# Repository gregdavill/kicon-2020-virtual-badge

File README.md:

# KiCon 2020 Virtual Badge by Greg Davill

Based off the design+template by [Thomas Flummer](https://gitlab.com/flummer/kicon-2020-virtual-badge)

I was inspired by the design Thomas made, and wanted to try and extend the badge with more LEDs. I'm using a similar architecture to the LED panels on the d20 and small LED cube I built, except this only has 1 colour of LED in the Matrix.

## Firmware

I've not coded up firmware for a display like this with a microcontroller before, and I've had trouble with the SAMD21's DMA controller and cyclic descriptors in the past. The display will require constant attention from the SAMD as it is a multiplexed display, I'm hoping that implementing a framebuffer + Binary Coded Modulation will be possible.

## Assembly

The LED matrix is 32x16. Or 512 individual LEDs, these are all 0402 in size, so manual assembly may not be for the casual electronics enthusiast.
At any rate I'd recommend using a solderpaste stencil and reflow oven.

## Making your own

If you want to make your own, I have included the gerbers, in case you don't want to install the nightly version.
The board is 4 layers mostly to assist in routing of the matrix. The cost difference between 2L and 4L at JLC is only $5 on their barebones service.

## Please share

If you decide to make this badge or a variant of it, please share images so we can all see it and get inspired. If sharing on social media, please use the #badgelife tag and please let [me](https://twitter.com/gregdavill) and [thomas](https://thomasflummer.com/) know, I would love to see what you have made!

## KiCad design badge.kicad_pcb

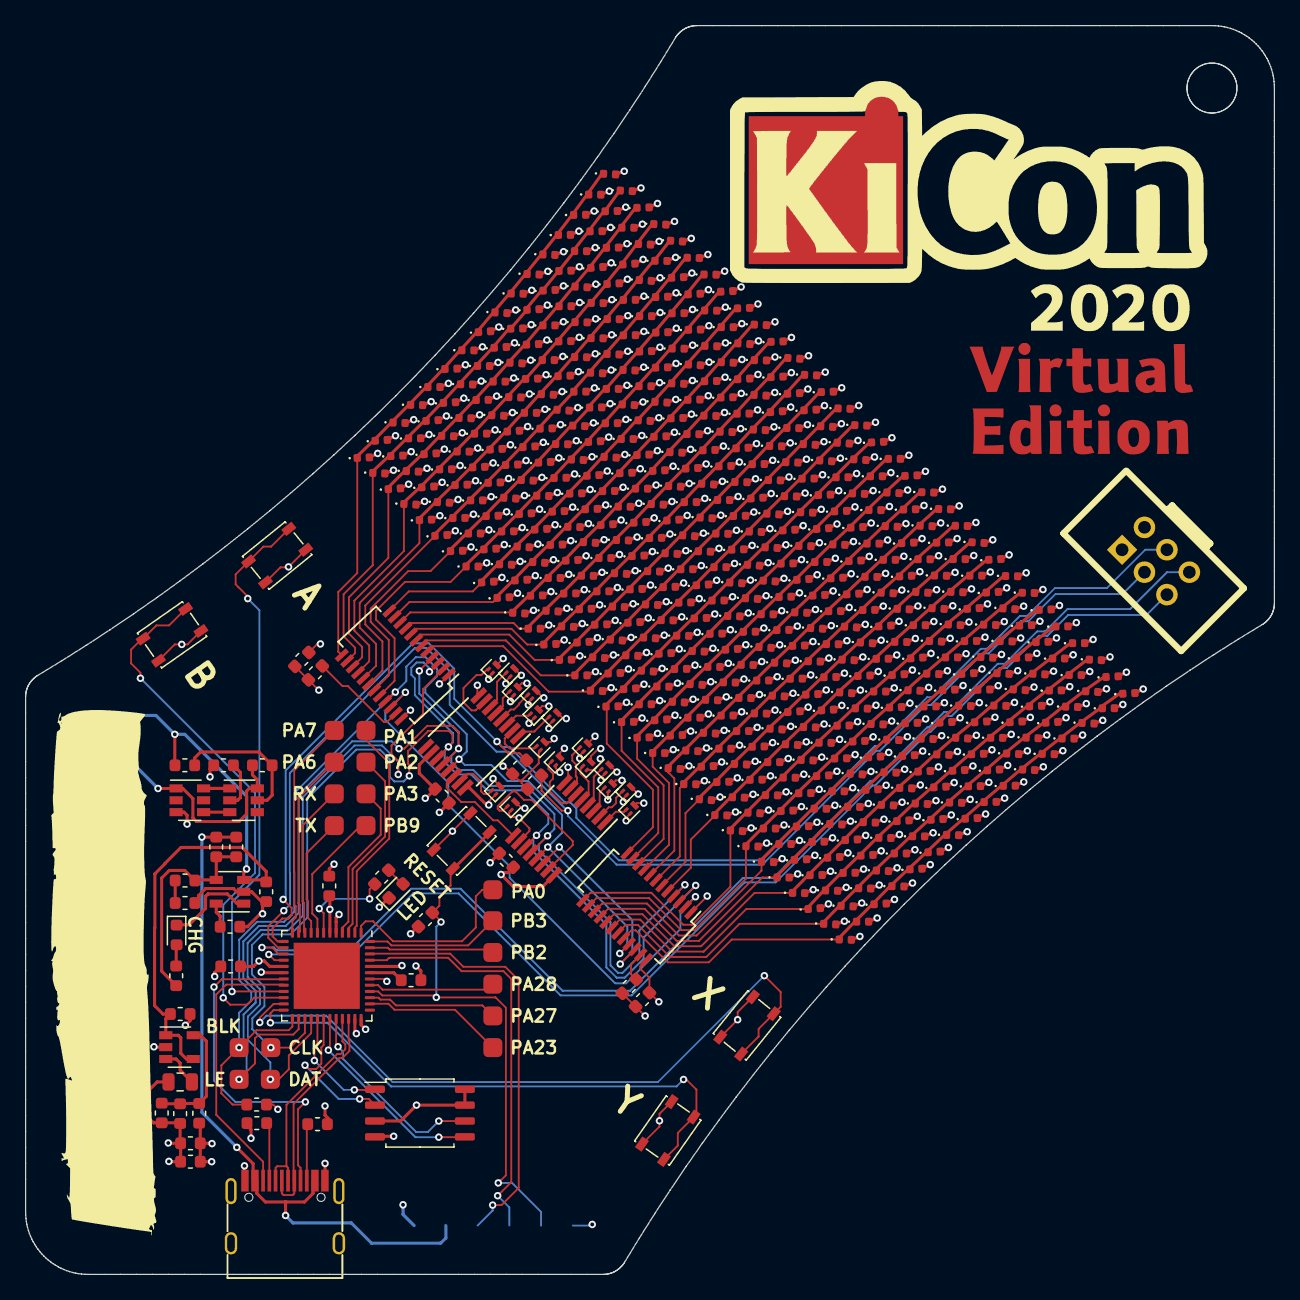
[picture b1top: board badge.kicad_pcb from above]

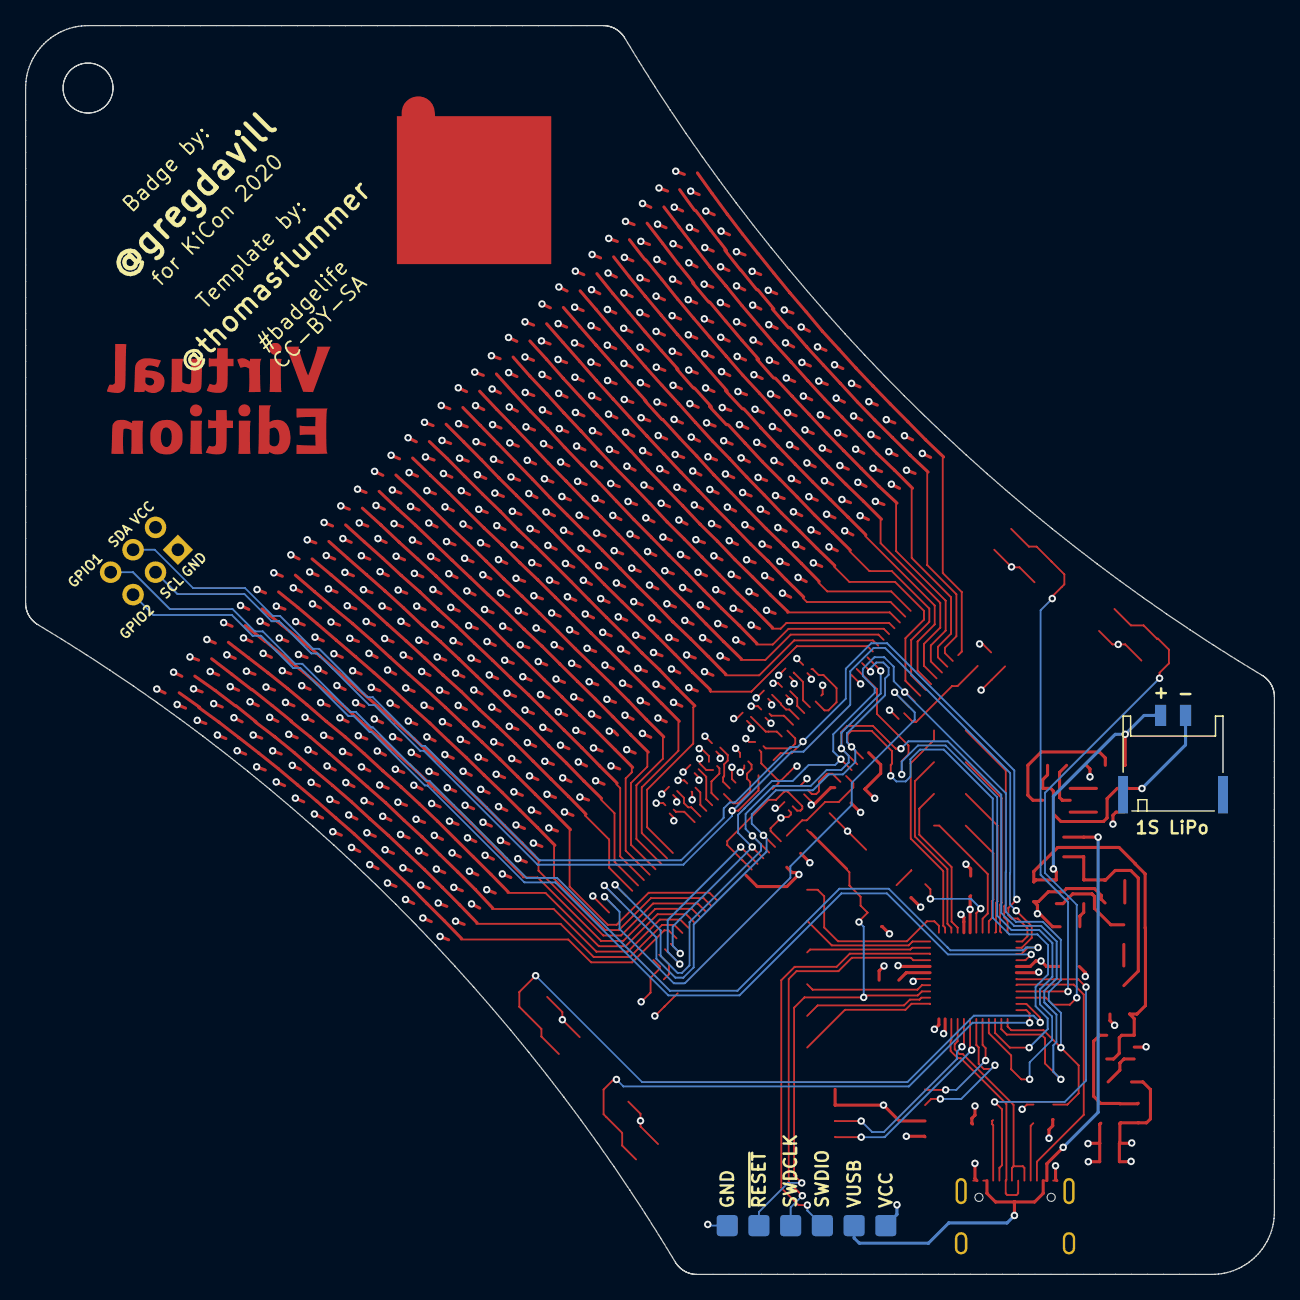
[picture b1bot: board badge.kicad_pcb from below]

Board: 4 copper layers, 100.0 x 100.0 mm, 600 parts (2 on the bottom side), 127 nets.

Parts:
C1, C2, C3, C4, C6, C8, C11: 100nF; C_0603_1608Metric
C5: 1uF; C_0603_1608Metric
C7, C9, C13, C14: 10uF; C_0603_1608Metric
C10: 10pF; C_0603_1608Metric
C12: 4.7uF; C_0603_1608Metric
D1, D2, D3, D4, D5, D6, D7, D8, D9, D10, D11, D12, D13, D14, D15, D16, D17, D18, D19, D20, D21, D22, D23, D24, D25, D26, D27, D28, D29, D30, D31, D32, D33, D34, D35, D36, D37, D38, D39, D40, D41, D42, D43, D44, D45, D46, D47, D48, D49, D50, D51, D52, D53, D54, D55, D56, D57, D58, D59, D60, D61, D62, D63, D64, D65, D66, D67, D68, D69, D70, D71, D72, D73, D74, D75, D76, D77, D78, D79, D80, D81, D82, D83, D84, D85, D86, D87, D88, D89, D90, D91, D92, D93, D94, D95, D96, D97, D98, D99, D100, D101, D102, D103, D104, D105, D106, D107, D108, D109, D110, D111, D112, D113, D114, D115, D116, D117, D118, D119, D120, D121, D122, D123, D124, D125, D126, D127, D128, D129, D130, D131, D132, D133, D134, D135, D136, D137, D138, D139, D140, D141, D142, D143, D144, D145, D146, D147, D148, D149, D150, D151, D152, D153, D154, D155, D156, D157, D158, D159, D160, D161, D162, D163, D164, D165, D166, D167, D168, D169, D170, D171, D172, D173, D174, D175, D176, D177, D178, D179, D180, D181, D182, D183, D184, D185, D186, D187, D188, D189, D190, D191, D192, D193, D194, D195, D196, D197, D198, D199, D200, D201, D202, D203, D204, D205, D206, D207, D208, D209, D210, D211, D212, D213, D214, D215, D216, D217, D218, D219, D220, D221, D222, D223, D224, D225, D226, D227, D228, D229, D230, D231, D232, D233, D234, D235, D236, D237, D238, D239, D240, D241, D242, D243, D244, D245, D246, D247, D248, D249, D250, D251, D252, D253, D254, D255, D256, D257, D258, D259, D260, D261, D262, D263, D264, D265, D266, D267, D268, D269, D270, D271, D272, D273, D274, D275, D276, D277, D278, D279, D280, D281, D282, D283, D284, D285, D286, D287, D288, D289, D290, D291, D292, D293, D294, D295, D296, D297, D298, D299, D300, D301, D302, D303, D304, D305, D306, D307, D308, D309, D310, D311, D312, D313, D314, D315, D316, D317, D318, D319, D320, D321, D322, D323, D324, D325, D326, D327, D328, D329, D330, D331, D332, D333, D334, D335, D336, D337, D338, D339, D340, D341, D342, D343, D344, D345, D346, D347, D348, D349, D350, D351, D352, D353, D354, D355, D356, D357, D358, D359, D360, D361, D362, D363, D364, D365, D366, D367, D368, D369, D370, D371, D372, D373, D374, D375, D376, D377, D378, D379, D380, D381, D382, D383, D384, D385, D386, D387, D388, D389, D390, D391, D392, D393, D394, D395, D396, D397, D398, D399, D400, D401, D402, D403, D404, D405, D406, D407, D408, D409, D410, D411, D412, D413, D414, D415, D416, D417, D418, D419, D420, D421, D422, D423, D424, D425, D426, D427, D428, D429, D430, D431, D432, D433, D434, D435, D436, D437, D438, D439, D440, D441, D442, D443, D444, D445, D446, D447, D448, D449, D450, D451, D452, D453, D454, D455, D456, D457, D458, D459, D460, D461, D462, D463, D464, D465, D466, D467, D468, D469, D470, D471, D472, D473, D474, D475, D476, D477, D478, D479, D480, D481, D482, D483, D484, D485, D486, D487, D488, D489, D490, D491, D492, D493, D494, D495, D496, D497, D498, D499, D500, D501, D502, D503, D504, D505, D506, D507, D508, D509, D510, D511, D512: LED; LED_0402_1005Metric
D513: LED; LED_0603_1608Metric
D514: CHRG; LED_0603_1608Metric
IC1: SAMD21G18A-MU; QFN-48-1EP_7x7mm_P0.5mm_EP5.3x5.3mm
J1: USB_C; USB_C_Receptacle_U262-161N-4BVC11
J2: DEBUG; PinHeader_1x06_P2.54mm_Vertical
J3: LiPo 1S; PH2.0-SMD-Horizontal
L1: 2.2uH; L_0805_2012Metric
Q1, Q2, Q3, Q4, Q5, Q6, Q7, Q8, Q9, Q10, Q11, Q12, Q13, Q14, Q15, Q16: 3412; SOT-883
R1, R2: R; R_0603_1608Metric
R3, R4: 5.1k; R_0603_1608Metric
R5: 10k; R_0603_1608Metric
R6, R11, R15: 1k; R_0603_1608Metric
R7, R8: 4.7k; R_0603_1608Metric
R9: 4.7K; R_0603_1608Metric
R10: 100; R_0603_1608Metric
R12, R13, R14: 1; R_0603_1608Metric
R16: 2k; R_0603_1608Metric
R17: 360k; R_0603_1608Metric
R18: 82k; R_0603_1608Metric
SW1: A; SW_SPST_PTS810
SW2: B; SW_SPST_PTS810
SW3: X; SW_SPST_PTS810
SW4: Y; SW_SPST_PTS810
SW5: RESET; SW_SPST_PTS810
TP1: RX; TestPoint_Large
TP2: TX; TestPoint_Large
TP3: DAT; TestPoint_Large
TP4: PB3; TestPoint_Large
TP5: PA1; TestPoint_Large
TP6: PB2; TestPoint_Large
TP7: PA2; TestPoint_Large
TP8: PA3; TestPoint_Large
TP9: PB9; TestPoint_Large
TP10: PA28; TestPoint_Large
TP11: PA27; TestPoint_Large
TP12: PA6; TestPoint_Large
TP13: PB23; TestPoint_Large
TP14: PA7; TestPoint_Large
TP15: PA0; TestPoint_Large
TP16: CLK; TestPoint_Large
TP17: LE; TestPoint_Large
TP18: BLK; TestPoint_Large
U1, U2: 74HC595; TSSOP-16_4.4x5mm_P0.65mm
U3, U4: TLC59025; SSOP-24_3.9x8.7mm_P0.635mm
U5: GD25Q32C; SOIC-8_5.23x5.23mm_P1.27mm
U6: DW01; SOT-23-6
U7: TLV62569DBV; SOT-23-5
U8: PM8205A; SOT-23-6
U9: HX4054A; SOT-23-5
X1: #badgelife; Badgelife-SAOv169-BADGE-2x3

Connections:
/1s LiPo/BATT_PLUS: C9.2, C12.1, J3.1, R10.1, U7.1 (EN), U7.4 (VIN), U9.3 (BAT)
/BTN_A: IC1.21 (PA12/I2C/EIC/SCOM2PAD0+/TC2), SW1.1 (A)
/BTN_B: IC1.22 (PA13/I2C/EIC/SCOM2PAD1+/TC2), SW2.1 (A)
/BTN_X: IC1.23 (PA14/XIN/EIC/SCOM2PAD2+/TC3), SW3.1 (A)
/BTN_Y: IC1.24 (PA15/XOUT/EIC/SCOM2PAD3+/TC3), SW4.1 (A)
/GPIO1: IC1.15 (PA10/EIC/AIN18/SCOM2PAD2+/TC1), X1.5 (GPIO1)
/GPIO2: IC1.16 (PA11/EIC/AIN19/SCOM2PAD3+/TC1), X1.6 (GPIO2)
/ISSI 12 RGB A/COM: D321.2 (A), D322.2 (A), D323.2 (A), D324.2 (A), D325.2 (A), D326.2 (A), D327.2 (A), D328.2 (A), D329.2 (A), D330.2 (A), D331.2 (A), D332.2 (A), D333.2 (A), D334.2 (A), D335.2 (A), D336.2 (A), D337.2 (A), D338.2 (A), D339.2 (A), D340.2 (A), D341.2 (A), D342.2 (A), D343.2 (A), D344.2 (A), D345.2 (A), D346.2 (A), D347.2 (A), D348.2 (A), D349.2 (A), D350.2 (A), D351.2 (A), D352.2 (A), Q6.3 (D)
/ISSI 12 RGB A/COM_1: D225.2 (A), D226.2 (A), D227.2 (A), D228.2 (A), D229.2 (A), D230.2 (A), D231.2 (A), D232.2 (A), D233.2 (A), D234.2 (A), D235.2 (A), D236.2 (A), D237.2 (A), D238.2 (A), D239.2 (A), D240.2 (A), D241.2 (A), D242.2 (A), D243.2 (A), D244.2 (A), D245.2 (A), D246.2 (A), D247.2 (A), D248.2 (A), D249.2 (A), D250.2 (A), D251.2 (A), D252.2 (A), D253.2 (A), D254.2 (A), D255.2 (A), D256.2 (A), Q15.3 (D)
/ISSI 12 RGB A/COM_2: D97.2 (A), D98.2 (A), D99.2 (A), D100.2 (A), D101.2 (A), D102.2 (A), D103.2 (A), D104.2 (A), D105.2 (A), D106.2 (A), D107.2 (A), D108.2 (A), D109.2 (A), D110.2 (A), D111.2 (A), D112.2 (A), D113.2 (A), D114.2 (A), D115.2 (A), D116.2 (A), D117.2 (A), D118.2 (A), D119.2 (A), D120.2 (A), D121.2 (A), D122.2 (A), D123.2 (A), D124.2 (A), D125.2 (A), D126.2 (A), D127.2 (A), D128.2 (A), Q7.3 (D)
/ISSI 12 RGB A/COM_3: D129.2 (A), D130.2 (A), D131.2 (A), D132.2 (A), D133.2 (A), D134.2 (A), D135.2 (A), D136.2 (A), D137.2 (A), D138.2 (A), D139.2 (A), D140.2 (A), D141.2 (A), D142.2 (A), D143.2 (A), D144.2 (A), D145.2 (A), D146.2 (A), D147.2 (A), D148.2 (A), D149.2 (A), D150.2 (A), D151.2 (A), D152.2 (A), D153.2 (A), D154.2 (A), D155.2 (A), D156.2 (A), D157.2 (A), D158.2 (A), D159.2 (A), D160.2 (A), Q9.3 (D)
/ISSI 12 RGB A/COM_4: D65.2 (A), D66.2 (A), D67.2 (A), D68.2 (A), D69.2 (A), D70.2 (A), D71.2 (A), D72.2 (A), D73.2 (A), D74.2 (A), D75.2 (A), D76.2 (A), D77.2 (A), D78.2 (A), D79.2 (A), D80.2 (A), D81.2 (A), D82.2 (A), D83.2 (A), D84.2 (A), D85.2 (A), D86.2 (A), D87.2 (A), D88.2 (A), D89.2 (A), D90.2 (A), D91.2 (A), D92.2 (A), D93.2 (A), D94.2 (A), D95.2 (A), D96.2 (A), Q5.3 (D)
/ISSI 12 RGB A/COM_5: D33.2 (A), D34.2 (A), D35.2 (A), D36.2 (A), D37.2 (A), D38.2 (A), D39.2 (A), D40.2 (A), D41.2 (A), D42.2 (A), D43.2 (A), D44.2 (A), D45.2 (A), D46.2 (A), D47.2 (A), D48.2 (A), D49.2 (A), D50.2 (A), D51.2 (A), D52.2 (A), D53.2 (A), D54.2 (A), D55.2 (A), D56.2 (A), D57.2 (A), D58.2 (A), D59.2 (A), D60.2 (A), D61.2 (A), D62.2 (A), D63.2 (A), D64.2 (A), Q3.3 (D)
/ISSI 12 RGB A/COM_6: D1.2 (A), D2.2 (A), D3.2 (A), D4.2 (A), D5.2 (A), D6.2 (A), D7.2 (A), D8.2 (A), D9.2 (A), D10.2 (A), D11.2 (A), D12.2 (A), D13.2 (A), D14.2 (A), D15.2 (A), D16.2 (A), D17.2 (A), D18.2 (A), D19.2 (A), D20.2 (A), D21.2 (A), D22.2 (A), D23.2 (A), D24.2 (A), D25.2 (A), D26.2 (A), D27.2 (A), D28.2 (A), D29.2 (A), D30.2 (A), D31.2 (A), D32.2 (A), Q1.3 (D)
/ISSI 12 RGB A/COM_7: D257.2 (A), D258.2 (A), D259.2 (A), D260.2 (A), D261.2 (A), D262.2 (A), D263.2 (A), D264.2 (A), D265.2 (A), D266.2 (A), D267.2 (A), D268.2 (A), D269.2 (A), D270.2 (A), D271.2 (A), D272.2 (A), D273.2 (A), D274.2 (A), D275.2 (A), D276.2 (A), D277.2 (A), D278.2 (A), D279.2 (A), D280.2 (A), D281.2 (A), D282.2 (A), D283.2 (A), D284.2 (A), D285.2 (A), D286.2 (A), D287.2 (A), D288.2 (A), Q2.3 (D)
/ISSI 12 RGB A/COM_8: D161.2 (A), D162.2 (A), D163.2 (A), D164.2 (A), D165.2 (A), D166.2 (A), D167.2 (A), D168.2 (A), D169.2 (A), D170.2 (A), D171.2 (A), D172.2 (A), D173.2 (A), D174.2 (A), D175.2 (A), D176.2 (A), D177.2 (A), D178.2 (A), D179.2 (A), D180.2 (A), D181.2 (A), D182.2 (A), D183.2 (A), D184.2 (A), D185.2 (A), D186.2 (A), D187.2 (A), D188.2 (A), D189.2 (A), D190.2 (A), D191.2 (A), D192.2 (A), Q11.3 (D)
/ISSI 12 RGB A/COM_9: D417.2 (A), D418.2 (A), D419.2 (A), D420.2 (A), D421.2 (A), D422.2 (A), D423.2 (A), D424.2 (A), D425.2 (A), D426.2 (A), D427.2 (A), D428.2 (A), D429.2 (A), D430.2 (A), D431.2 (A), D432.2 (A), D433.2 (A), D434.2 (A), D435.2 (A), D436.2 (A), D437.2 (A), D438.2 (A), D439.2 (A), D440.2 (A), D441.2 (A), D442.2 (A), D443.2 (A), D444.2 (A), D445.2 (A), D446.2 (A), D447.2 (A), D448.2 (A), Q12.3 (D)
/ISSI 12 RGB A/COM_10: D449.2 (A), D450.2 (A), D451.2 (A), D452.2 (A), D453.2 (A), D454.2 (A), D455.2 (A), D456.2 (A), D457.2 (A), D458.2 (A), D459.2 (A), D460.2 (A), D461.2 (A), D462.2 (A), D463.2 (A), D464.2 (A), D465.2 (A), D466.2 (A), D467.2 (A), D468.2 (A), D469.2 (A), D470.2 (A), D471.2 (A), D472.2 (A), D473.2 (A), D474.2 (A), D475.2 (A), D476.2 (A), D477.2 (A), D478.2 (A), D479.2 (A), D480.2 (A), Q14.3 (D)
/ISSI 12 RGB A/COM_11: D481.2 (A), D482.2 (A), D483.2 (A), D484.2 (A), D485.2 (A), D486.2 (A), D487.2 (A), D488.2 (A), D489.2 (A), D490.2 (A), D491.2 (A), D492.2 (A), D493.2 (A), D494.2 (A), D495.2 (A), D496.2 (A), D497.2 (A), D498.2 (A), D499.2 (A), D500.2 (A), D501.2 (A), D502.2 (A), D503.2 (A), D504.2 (A), D505.2 (A), D506.2 (A), D507.2 (A), D508.2 (A), D509.2 (A), D510.2 (A), D511.2 (A), D512.2 (A), Q16.3 (D)
/ISSI 12 RGB A/COM_12: D353.2 (A), D354.2 (A), D355.2 (A), D356.2 (A), D357.2 (A), D358.2 (A), D359.2 (A), D360.2 (A), D361.2 (A), D362.2 (A), D363.2 (A), D364.2 (A), D365.2 (A), D366.2 (A), D367.2 (A), D368.2 (A), D369.2 (A), D370.2 (A), D371.2 (A), D372.2 (A), D373.2 (A), D374.2 (A), D375.2 (A), D376.2 (A), D377.2 (A), D378.2 (A), D379.2 (A), D380.2 (A), D381.2 (A), D382.2 (A), D383.2 (A), D384.2 (A), Q8.3 (D)
/ISSI 12 RGB A/COM_13: D385.2 (A), D386.2 (A), D387.2 (A), D388.2 (A), D389.2 (A), D390.2 (A), D391.2 (A), D392.2 (A), D393.2 (A), D394.2 (A), D395.2 (A), D396.2 (A), D397.2 (A), D398.2 (A), D399.2 (A), D400.2 (A), D401.2 (A), D402.2 (A), D403.2 (A), D404.2 (A), D405.2 (A), D406.2 (A), D407.2 (A), D408.2 (A), D409.2 (A), D410.2 (A), D411.2 (A), D412.2 (A), D413.2 (A), D414.2 (A), D415.2 (A), D416.2 (A), Q10.3 (D)
/ISSI 12 RGB A/COM_14: D193.2 (A), D194.2 (A), D195.2 (A), D196.2 (A), D197.2 (A), D198.2 (A), D199.2 (A), D200.2 (A), D201.2 (A), D202.2 (A), D203.2 (A), D204.2 (A), D205.2 (A), D206.2 (A), D207.2 (A), D208.2 (A), D209.2 (A), D210.2 (A), D211.2 (A), D212.2 (A), D213.2 (A), D214.2 (A), D215.2 (A), D216.2 (A), D217.2 (A), D218.2 (A), D219.2 (A), D220.2 (A), D221.2 (A), D222.2 (A), D223.2 (A), D224.2 (A), Q13.3 (D)
/ISSI 12 RGB A/COM_15: D289.2 (A), D290.2 (A), D291.2 (A), D292.2 (A), D293.2 (A), D294.2 (A), D295.2 (A), D296.2 (A), D297.2 (A), D298.2 (A), D299.2 (A), D300.2 (A), D301.2 (A), D302.2 (A), D303.2 (A), D304.2 (A), D305.2 (A), D306.2 (A), D307.2 (A), D308.2 (A), D309.2 (A), D310.2 (A), D311.2 (A), D312.2 (A), D313.2 (A), D314.2 (A), D315.2 (A), D316.2 (A), D317.2 (A), D318.2 (A), D319.2 (A), D320.2 (A), Q4.3 (D)
/ISSI 12 RGB A/DAT_OUT: U1.14 (SER), U4.22 (SDO)
/LED_BLANK: IC1.25 (PA16/I2C/EIC/SCOM1PAD0+/TC2), R9.2, TP18.1, U1.13 (~OE), U2.13 (~OE), U3.21 (~OE), U4.21 (~OE)
/LED_DAT: IC1.28 (PA19/EIC/SCOM1PAD3+/TC3), TP3.1, U3.2 (SDI)
/LED_LATCH: IC1.26 (PA17/I2C/EIC/SCOM1PAD1+/TC2), TP17.1, U1.12 (RCLK), U2.12 (RCLK), U3.4 (LE), U4.4 (LE)
/LED_SCLK: IC1.27 (PA18/EIC/SCOM1PAD2+/TC3), TP16.1, U1.11 (SRCLK), U2.11 (SRCLK), U3.3 (CLK), U4.3 (CLK)
/SAMD21/FLASH_CS: IC1.29 (PA20/EIC/SCOM5PAD2+), U5.1 (~CS~)
/SAMD21/FLASH_MISO: IC1.30 (PA21/EIC/SCOM5PAD3+), U5.2 (DO/IO1)
/SAMD21/FLASH_MOSI: IC1.31 (PA22/I2C/EIC/SCOM5PAD0+/TC4), U5.5 (DI/IO0)
/SAMD21/FLASH_SCK: IC1.32 (PA23/I2C/EIC/SCOM5PAD1+/TC4), U5.6 (SCK)
/SAMD21/SBU1: IC1.19 (PB10/EIC/SCOM4PAD2/TC5), J1.A8 (SBU1)
/SAMD21/SBU2: IC1.20 (PB11/EIC/SCOM4PAD3/TC5), J1.B8 (SBU2)
/SAMD21/SWDCLK: IC1.45 (PA30/EIC/SCOM1PAD2/TC1), J2.4
/SAMD21/SWDIO: IC1.46 (PA31/EIC/SCOM1PAD3/TC1), J2.3
/SAMD21/USB_D+: IC1.34 (PA25/EIC/SCOM3PAD3+/TC5), J1.A6 (D+), J1.B6 (D+)
/SAMD21/USB_D-: IC1.33 (PA24/EIC/SCOM3PAD2+/TC5), J1.A7 (D-), J1.B7 (D-)
/SAMD21/~RESET: IC1.40 (RESETN), J2.5, R5.1, SW5.1 (A)
/SCL: IC1.14 (PA9/I2C/EIC/AIN17/SCOM2PAD1+/TC0), R8.1, X1.4 (SCL)
/SDA: IC1.13 (PA8/I2C/AIN16/SCOM2PAD0+/TC0), R7.1, X1.3 (SDA)
/UART_RX: IC1.10 (PA5/EIC/AIN5/SCOM0PAD1/TC0), TP1.1
/UART_TX: IC1.9 (PA4/EIC/REF/AIN4/SCOM0PAD0/TC0), TP2.1
/VUSB: J1.A4 (VBUS), J1.A9 (VBUS), J1.B4 (VBUS), J1.B9 (VBUS), J2.2, R12.2, R13.2
COL_GA0: D1.1 (K), D33.1 (K), D65.1 (K), D97.1 (K), D129.1 (K), D161.1 (K), D193.1 (K), D225.1 (K), D257.1 (K), D289.1 (K), D321.1 (K), D353.1 (K), D385.1 (K), D417.1 (K), D449.1 (K), D481.1 (K), U3.13 (OUT8)
COL_GA1: D2.1 (K), D34.1 (K), D66.1 (K), D98.1 (K), D130.1 (K), D162.1 (K), D194.1 (K), D226.1 (K), D258.1 (K), D290.1 (K), D322.1 (K), D354.1 (K), D386.1 (K), D418.1 (K), D450.1 (K), D482.1 (K), U3.14 (OUT9)
COL_GA2: D3.1 (K), D35.1 (K), D67.1 (K), D99.1 (K), D131.1 (K), D163.1 (K), D195.1 (K), D227.1 (K), D259.1 (K), D291.1 (K), D323.1 (K), D355.1 (K), D387.1 (K), D419.1 (K), D451.1 (K), D483.1 (K), U3.15 (OUT10)
COL_GA3: D4.1 (K), D36.1 (K), D68.1 (K), D100.1 (K), D132.1 (K), D164.1 (K), D196.1 (K), D228.1 (K), D260.1 (K), D292.1 (K), D324.1 (K), D356.1 (K), D388.1 (K), D420.1 (K), D452.1 (K), D484.1 (K), U3.16 (OUT11)
COL_GA4: D5.1 (K), D37.1 (K), D69.1 (K), D101.1 (K), D133.1 (K), D165.1 (K), D197.1 (K), D229.1 (K), D261.1 (K), D293.1 (K), D325.1 (K), D357.1 (K), D389.1 (K), D421.1 (K), D453.1 (K), D485.1 (K), U3.17 (OUT12)
COL_GA5: D6.1 (K), D38.1 (K), D70.1 (K), D102.1 (K), D134.1 (K), D166.1 (K), D198.1 (K), D230.1 (K), D262.1 (K), D294.1 (K), D326.1 (K), D358.1 (K), D390.1 (K), D422.1 (K), D454.1 (K), D486.1 (K), U3.18 (OUT13)
COL_GA6: D7.1 (K), D39.1 (K), D71.1 (K), D103.1 (K), D135.1 (K), D167.1 (K), D199.1 (K), D231.1 (K), D263.1 (K), D295.1 (K), D327.1 (K), D359.1 (K), D391.1 (K), D423.1 (K), D455.1 (K), D487.1 (K), U3.19 (OUT14)
COL_GA7: D8.1 (K), D40.1 (K), D72.1 (K), D104.1 (K), D136.1 (K), D168.1 (K), D200.1 (K), D232.1 (K), D264.1 (K), D296.1 (K), D328.1 (K), D360.1 (K), D392.1 (K), D424.1 (K), D456.1 (K), D488.1 (K), U3.20 (OUT15)
COL_GA8: D9.1 (K), D41.1 (K), D73.1 (K), D105.1 (K), D137.1 (K), D169.1 (K), D201.1 (K), D233.1 (K), D265.1 (K), D297.1 (K), D329.1 (K), D361.1 (K), D393.1 (K), D425.1 (K), D457.1 (K), D489.1 (K), U3.12 (OUT7)
COL_GA9: D10.1 (K), D42.1 (K), D74.1 (K), D106.1 (K), D138.1 (K), D170.1 (K), D202.1 (K), D234.1 (K), D266.1 (K), D298.1 (K), D330.1 (K), D362.1 (K), D394.1 (K), D426.1 (K), D458.1 (K), D490.1 (K), U3.11 (OUT6)
COL_GA10: D11.1 (K), D43.1 (K), D75.1 (K), D107.1 (K), D139.1 (K), D171.1 (K), D203.1 (K), D235.1 (K), D267.1 (K), D299.1 (K), D331.1 (K), D363.1 (K), D395.1 (K), D427.1 (K), D459.1 (K), D491.1 (K), U3.10 (OUT5)
COL_GA11: D12.1 (K), D44.1 (K), D76.1 (K), D108.1 (K), D140.1 (K), D172.1 (K), D204.1 (K), D236.1 (K), D268.1 (K), D300.1 (K), D332.1 (K), D364.1 (K), D396.1 (K), D428.1 (K), D460.1 (K), D492.1 (K), U3.9 (OUT4)
COL_GA12: D13.1 (K), D45.1 (K), D77.1 (K), D109.1 (K), D141.1 (K), D173.1 (K), D205.1 (K), D237.1 (K), D269.1 (K), D301.1 (K), D333.1 (K), D365.1 (K), D397.1 (K), D429.1 (K), D461.1 (K), D493.1 (K), U3.8 (OUT3)
COL_GA13: D14.1 (K), D46.1 (K), D78.1 (K), D110.1 (K), D142.1 (K), D174.1 (K), D206.1 (K), D238.1 (K), D270.1 (K), D302.1 (K), D334.1 (K), D366.1 (K), D398.1 (K), D430.1 (K), D462.1 (K), D494.1 (K), U3.7 (OUT2)
COL_GA14: D15.1 (K), D47.1 (K), D79.1 (K), D111.1 (K), D143.1 (K), D175.1 (K), D207.1 (K), D239.1 (K), D271.1 (K), D303.1 (K), D335.1 (K), D367.1 (K), D399.1 (K), D431.1 (K), D463.1 (K), D495.1 (K), U3.6 (OUT1)
COL_GA15: D16.1 (K), D48.1 (K), D80.1 (K), D112.1 (K), D144.1 (K), D176.1 (K), D208.1 (K), D240.1 (K), D272.1 (K), D304.1 (K), D336.1 (K), D368.1 (K), D400.1 (K), D432.1 (K), D464.1 (K), D496.1 (K), U3.5 (OUT0)
COL_GA16: D17.1 (K), D49.1 (K), D81.1 (K), D113.1 (K), D145.1 (K), D177.1 (K), D209.1 (K), D241.1 (K), D273.1 (K), D305.1 (K), D337.1 (K), D369.1 (K), D401.1 (K), D433.1 (K), D465.1 (K), D497.1 (K), U4.12 (OUT7)
COL_GA17: D18.1 (K), D50.1 (K), D82.1 (K), D114.1 (K), D146.1 (K), D178.1 (K), D210.1 (K), D242.1 (K), D274.1 (K), D306.1 (K), D338.1 (K), D370.1 (K), D402.1 (K), D434.1 (K), D466.1 (K), D498.1 (K), U4.11 (OUT6)
COL_GA18: D19.1 (K), D51.1 (K), D83.1 (K), D115.1 (K), D147.1 (K), D179.1 (K), D211.1 (K), D243.1 (K), D275.1 (K), D307.1 (K), D339.1 (K), D371.1 (K), D403.1 (K), D435.1 (K), D467.1 (K), D499.1 (K), U4.10 (OUT5)
COL_GA19: D20.1 (K), D52.1 (K), D84.1 (K), D116.1 (K), D148.1 (K), D180.1 (K), D212.1 (K), D244.1 (K), D276.1 (K), D308.1 (K), D340.1 (K), D372.1 (K), D404.1 (K), D436.1 (K), D468.1 (K), D500.1 (K), U4.9 (OUT4)
COL_GA20: D21.1 (K), D53.1 (K), D85.1 (K), D117.1 (K), D149.1 (K), D181.1 (K), D213.1 (K), D245.1 (K), D277.1 (K), D309.1 (K), D341.1 (K), D373.1 (K), D405.1 (K), D437.1 (K), D469.1 (K), D501.1 (K), U4.8 (OUT3)
COL_GA21: D22.1 (K), D54.1 (K), D86.1 (K), D118.1 (K), D150.1 (K), D182.1 (K), D214.1 (K), D246.1 (K), D278.1 (K), D310.1 (K), D342.1 (K), D374.1 (K), D406.1 (K), D438.1 (K), D470.1 (K), D502.1 (K), U4.7 (OUT2)
COL_GA22: D23.1 (K), D55.1 (K), D87.1 (K), D119.1 (K), D151.1 (K), D183.1 (K), D215.1 (K), D247.1 (K), D279.1 (K), D311.1 (K), D343.1 (K), D375.1 (K), D407.1 (K), D439.1 (K), D471.1 (K), D503.1 (K), U4.6 (OUT1)
COL_GA23: D24.1 (K), D56.1 (K), D88.1 (K), D120.1 (K), D152.1 (K), D184.1 (K), D216.1 (K), D248.1 (K), D280.1 (K), D312.1 (K), D344.1 (K), D376.1 (K), D408.1 (K), D440.1 (K), D472.1 (K), D504.1 (K), U4.5 (OUT0)
COL_GA24: D25.1 (K), D57.1 (K), D89.1 (K), D121.1 (K), D153.1 (K), D185.1 (K), D217.1 (K), D249.1 (K), D281.1 (K), D313.1 (K), D345.1 (K), D377.1 (K), D409.1 (K), D441.1 (K), D473.1 (K), D505.1 (K), U4.13 (OUT8)
COL_GA25: D26.1 (K), D58.1 (K), D90.1 (K), D122.1 (K), D154.1 (K), D186.1 (K), D218.1 (K), D250.1 (K), D282.1 (K), D314.1 (K), D346.1 (K), D378.1 (K), D410.1 (K), D442.1 (K), D474.1 (K), D506.1 (K), U4.14 (OUT9)
COL_GA26: D27.1 (K), D59.1 (K), D91.1 (K), D123.1 (K), D155.1 (K), D187.1 (K), D219.1 (K), D251.1 (K), D283.1 (K), D315.1 (K), D347.1 (K), D379.1 (K), D411.1 (K), D443.1 (K), D475.1 (K), D507.1 (K), U4.15 (OUT10)
COL_GA27: D28.1 (K), D60.1 (K), D92.1 (K), D124.1 (K), D156.1 (K), D188.1 (K), D220.1 (K), D252.1 (K), D284.1 (K), D316.1 (K), D348.1 (K), D380.1 (K), D412.1 (K), D444.1 (K), D476.1 (K), D508.1 (K), U4.16 (OUT11)
COL_GA28: D29.1 (K), D61.1 (K), D93.1 (K), D125.1 (K), D157.1 (K), D189.1 (K), D221.1 (K), D253.1 (K), D285.1 (K), D317.1 (K), D349.1 (K), D381.1 (K), D413.1 (K), D445.1 (K), D477.1 (K), D509.1 (K), U4.17 (OUT12)
COL_GA29: D30.1 (K), D62.1 (K), D94.1 (K), D126.1 (K), D158.1 (K), D190.1 (K), D222.1 (K), D254.1 (K), D286.1 (K), D318.1 (K), D350.1 (K), D382.1 (K), D414.1 (K), D446.1 (K), D478.1 (K), D510.1 (K), U4.18 (OUT13)
COL_GA30: D31.1 (K), D63.1 (K), D95.1 (K), D127.1 (K), D159.1 (K), D191.1 (K), D223.1 (K), D255.1 (K), D287.1 (K), D319.1 (K), D351.1 (K), D383.1 (K), D415.1 (K), D447.1 (K), D479.1 (K), D511.1 (K), U4.19 (OUT14)
COL_GA31: D32.1 (K), D64.1 (K), D96.1 (K), D128.1 (K), D160.1 (K), D192.1 (K), D224.1 (K), D256.1 (K), D288.1 (K), D320.1 (K), D352.1 (K), D384.1 (K), D416.1 (K), D448.1 (K), D480.1 (K), D512.1 (K), U4.20 (OUT15)
GND: C1.2, C2.2, C3.2, C4.2, C5.2, C6.2, C7.2, C9.1, C11.2, C12.2, C13.1, C14.1, D513.1 (K), IC1.5 (GNDANA), IC1.18 (GND1), IC1.35 (GND2), IC1.42 (GND3), J1.A1 (GND), J1.A12 (GND), J1.B1 (GND), J1.B12 (GND), J1.S1 (SHIELD), J2.6, R1.2, R2.2, R3.1, R4.1, R11.1, R16.1, R18.2, SW1.2 (B), SW2.2 (B), SW3.2 (B), SW4.2 (B), SW5.2 (B), U1.8 (GND), U2.8 (GND), U3.1 (GND), U4.1 (GND), U5.4 (GND), U7.2 (GND), U8.3 (S2), U9.2 (GND), X1.2 (GND)
unnamed: C5.1, IC1.43 (VDDCORE1)
unnamed: C8.1, R10.2, U6.5 (VCC)
unnamed: C8.2, J3.2, U6.6 (GND), U8.1 (S1)
unnamed: C10.1, R17.1, R18.1, U7.5 (FB)
unnamed: C11.1, R14.1
unnamed: D513.2 (A), R6.1
unnamed: D514.1 (K), U9.1 (~CHRG)
unnamed: D514.2 (A), R15.1
unnamed: IC1.1 (PA0/XIN32/EIC/SCOM1PAD0/TC2), TP15.1
unnamed: IC1.2 (PA1/XOUT32/EIC/SCOM1PAD1/TC2), TP5.1
unnamed: IC1.3 (PA2/EIC/AIN0), TP7.1
unnamed: IC1.4 (PA3/EIC/REF/AIN1), TP8.1
unnamed: IC1.7 (PB8/EIC/AIN2/SCOM4PAD0/TC4), R6.2
unnamed: IC1.8 (PB9/EIC/AIN3/SCOM4PAD1//TC4), TP9.1
unnamed: IC1.11 (PA6/EIC/AIN6/SCOM0PAD2/TC1), TP12.1
unnamed: IC1.12 (PA7/EIC/AIN7/SCOM0PAD3/TC1), TP14.1
unnamed: IC1.38 (PB23/EIC/SCOM5PAD3), TP13.1
unnamed: IC1.39 (PA27/EIC), TP11.1
unnamed: IC1.41 (PA28/EIC), TP10.1
unnamed: IC1.47 (PB2/EIC/AIN10/SCOM5PAD0), TP6.1
unnamed: IC1.48 (PB3/EIC/AIN11/SCOM5PAD1), TP4.1
unnamed: J1.A5 (CC1), R3.2
unnamed: J1.B5 (CC2), R4.2
unnamed: L1.1, U7.3 (SW)
unnamed: Q1.1 (G), U1.15 (QA)
unnamed: Q2.1 (G), U2.15 (QA)
unnamed: Q3.1 (G), U1.1 (QB)
unnamed: Q4.1 (G), U2.1 (QB)
unnamed: Q5.1 (G), U1.2 (QC)
unnamed: Q6.1 (G), U2.2 (QC)
unnamed: Q7.1 (G), U1.3 (QD)
unnamed: Q8.1 (G), U2.3 (QD)
unnamed: Q9.1 (G), U1.4 (QE)
unnamed: Q10.1 (G), U2.4 (QE)
unnamed: Q11.1 (G), U1.5 (QF)
unnamed: Q12.1 (G), U2.5 (QF)
unnamed: Q13.1 (G), U1.6 (QG)
unnamed: Q14.1 (G), U2.6 (QG)
unnamed: Q15.1 (G), U1.7 (QH)
unnamed: Q16.1 (G), U2.7 (QH)
unnamed: R1.1, U3.23 (R-EXT)
unnamed: R2.1, U4.23 (R-EXT)
unnamed: R11.2, U6.2 (CS)
unnamed: R12.1, R13.1, R14.2, R15.2, U9.4 (VCC)
unnamed: R16.2, U9.5 (PROG)
unnamed: U1.9 (QH'), U2.14 (SER)
unnamed: U3.22 (SDO), U4.2 (SDI)
unnamed: U6.1 (OD), U8.6 (G1)
unnamed: U6.3 (OC), U8.4 (G2)
VCC: C1.1, C2.1, C3.1, C4.1, C6.1, C7.1, C10.2, C13.2, C14.2, IC1.6 (VDDANA), IC1.17 (VDDIO1), IC1.36 (VDDIO2), IC1.44 (VDDIN), J2.1, L1.2, Q1.2 (S), Q2.2 (S), Q3.2 (S), Q4.2 (S), Q5.2 (S), Q6.2 (S), Q7.2 (S), Q8.2 (S), Q9.2 (S), Q10.2 (S), Q11.2 (S), Q12.2 (S), Q13.2 (S), Q14.2 (S), Q15.2 (S), Q16.2 (S), R5.2, R7.2, R8.2, R9.1, R17.2, U1.10 (~SRCLR), U1.16 (VCC), U2.10 (~SRCLR), U2.16 (VCC), U3.24 (VDD), U4.24 (VDD), U5.3 (~WP~/IO2), U5.7 (~HOLD~/IO3), U5.8 (VDD), X1.1 (VCC)

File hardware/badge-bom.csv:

Reference, Quantity, Value, Footprint, Datasheet, Mfg, PN, VALUE
C10 ,1,"10pF","Capacitor_SMD:C_0603_1608Metric","~","Samsung Electro-Mechanics","CL10C100JB81PNC",""
C12 ,1,"4.7uF","Capacitor_SMD:C_0603_1608Metric","~","Samsung Electro-Mechanics","CL10A475KO8NNNC",""
C5 ,1,"1uF","Capacitor_SMD:C_0603_1608Metric","~","Samsung Electro-Mechanics","CL10B105KO8NNNC",""
C6 C1 C2 C3 C4 C8 C11 ,7,"100nF","Capacitor_SMD:C_0603_1608Metric","~","Samsung Electro-Mechanics","CL10B104KB8NNNC",""
C7 C9 C13 C14 ,4,"10uF","Capacitor_SMD:C_0603_1608Metric","~","Samsung Electro-Mechanics","CL10A106MO8NQNC",""
D1 D2 D3 D4 D5 D6 D7 D8 D9 D10 D11 D12 D13 D14 D15 D16 D17 D18 D19 D20 D21 D22 D23 D24 D25 D26 D27 D28 D29 D30 D31 D32 D33 D34 D35 D36 D37 D38 D39 D40 D41 D42 D43 D44 D45 D46 D47 D48 D49 D50 D51 D52 D53 D54 D55 D56 D57 D58 D59 D60 D61 D62 D63 D64 D65 D66 D67 D68 D69 D70 D71 D72 D73 D74 D75 D76 D77 D78 D79 D80 D81 D82 D83 D84 D85 D86 D87 D88 D89 D90 D91 D92 D93 D94 D95 D96 D97 D98 D99 D100 D101 D102 D103 D104 D105 D106 D107 D108 D109 D110 D111 D112 D113 D114 D115 D116 D117 D118 D119 D120 D121 D122 D123 D124 D125 D126 D127 D128 D129 D130 D131 D132 D133 D134 D135 D136 D137 D138 D139 D140 D141 D142 D143 D144 D145 D146 D147 D148 D149 D150 D151 D152 D153 D154 D155 D156 D157 D158 D159 D160 D161 D162 D163 D164 D165 D166 D167 D168 D169 D170 D171 D172 D173 D174 D175 D176 D177 D178 D179 D180 D181 D182 D183 D184 D185 D186 D187 D188 D189 D190 D191 D192 D193 D194 D195 D196 D197 D198 D199 D200 D201 D202 D203 D204 D205 D206 D207 D208 D209 D210 D211 D212 D213 D214 D215 D216 D217 D218 D219 D220 D221 D222 D223 D224 D225 D226 D227 D228 D229 D230 D231 D232 D233 D234 D235 D236 D237 D238 D239 D240 D241 D242 D243 D244 D245 D246 D247 D248 D249 D250 D251 D252 D253 D254 D255 D256 D257 D258 D259 D260 D261 D262 D263 D264 D265 D266 D267 D268 D269 D270 D271 D272 D273 D274 D275 D276 D277 D278 D279 D280 D281 D282 D283 D284 D285 D286 D287 D288 D289 D290 D291 D292 D293 D294 D295 D296 D297 D298 D299 D300 D301 D302 D303 D304 D305 D306 D307 D308 D309 D310 D311 D312 D313 D314 D315 D316 D317 D318 D319 D320 D321 D322 D323 D324 D325 D326 D327 D328 D329 D330 D331 D332 D333 D334 D335 D336 D337 D338 D339 D340 D341 D342 D343 D344 D345 D346 D347 D348 D349 D350 D351 D352 D353 D354 D355 D356 D357 D358 D359 D360 D361 D362 D363 D364 D365 D366 D367 D368 D369 D370 D371 D372 D373 D374 D375 D376 D377 D378 D379 D380 D381 D382 D383 D384 D385 D386 D387 D388 D389 D390 D391 D392 D393 D394 D395 D396 D397 D398 D399 D400 D401 D402 D403 D404 D405 D406 D407 D408 D409 D410 D411 D412 D413 D414 D415 D416 D417 D418 D419 D420 D421 D422 D423 D424 D425 D426 D427 D428 D429 D430 D431 D432 D433 D434 D435 D436 D437 D438 D439 D440 D441 D442 D443 D444 D445 D446 D447 D448 D449 D450 D451 D452 D453 D454 D455 D456 D457 D458 D459 D460 D461 D462 D463 D464 D465 D466 D467 D468 D469 D470 D471 D472 D473 D474 D475 D476 D477 D478 D479 D480 D481 D482 D483 D484 D485 D486 D487 D488 D489 D490 D491 D492 D493 D494 D495 D496 D497 D498 D499 D500 D501 D502 D503 D504 D505 D506 D507 D508 D509 D510 D511 D512 ,512,"LED","LED_SMD:LED_0402_1005Metric","~","Foshan NationStar Optoelectronics","NCD0402O1",""
D513 ,1,"LED","LED_SMD:LED_0603_1608Metric","~","Foshan NationStar Optoelectronics","NCD0603C1",""
D514 ,1,"CHRG","LED_SMD:LED_0603_1608Metric","~","Foshan NationStar Optoelectronics","NCD0603Y1",""
IC1 ,1,"SAMD21G18A","Package_DFN_QFN:QFN-48-1EP_7x7mm_P0.5mm_EP5.3x5.3mm","","Microchip Tech","ATSAMD21G16L-MNT","SAMD21G18A-MU"
J1 ,1,"USB_C","Connectors:USB_C_Receptacle_U262-161N-4BVC11","https://www.usb.org/sites/default/files/documents/usb_type-c.zip","XKB Connectivity","U262-161N-4BVC11",""
J2 ,1,"DEBUG","Connector_PinHeader_2.54mm:PinHeader_1x06_P2.54mm_Vertical","~"
J3 ,1,"LiPo 1S","Connectors:PH2.0-SMD-Horizontal","~","JST Sales America","S2B-PH-SM4-TB(LF)(SN)",""
L1 ,1,"2.2uH","Inductor_SMD:L_0805_2012Metric","~","Sunltech Tech","SLM20122R2MIT",""
Q1 Q2 Q3 Q4 Q5 Q6 Q7 Q8 Q9 Q10 Q11 Q12 Q13 Q14 Q15 Q16 ,16,"3412","Package_TO_SOT_SMD:SOT-883","~","LRC","LP0404N3T5G",""
R1 R2 R16 ,3,"2k","Resistor_SMD:R_0603_1608Metric","~","UNI-ROYAL(Uniroyal Elec)","0603WAF2001T5E",""
R10 ,1,"100","Resistor_SMD:R_0603_1608Metric","~","UNI-ROYAL(Uniroyal Elec)","0603WAF1000T5E",""
R12 R13 R14 ,3,"1","Resistor_SMD:R_0603_1608Metric","~","UNI-ROYAL(Uniroyal Elec)","0603WAF0000T5E",""
R17 ,1,"360k","Resistor_SMD:R_0603_1608Metric","~","UNI-ROYAL(Uniroyal Elec)","0603WAF3603T5E",""
R18 ,1,"82k","Resistor_SMD:R_0603_1608Metric","~","UNI-ROYAL(Uniroyal Elec)","0603WAF8202T5E",""
R3 R4 ,2,"5.1k","Resistor_SMD:R_0603_1608Metric","~","UNI-ROYAL(Uniroyal Elec)","0603WAF5101T5E",""
R5 ,1,"10k","Resistor_SMD:R_0603_1608Metric","~","UNI-ROYAL(Uniroyal Elec)","0603WAF1002T5E",""
R6 R11 R15 ,3,"1k","Resistor_SMD:R_0603_1608Metric","~","UNI-ROYAL(Uniroyal Elec)","0603WAF1001T5E",""
R7 R8 R9 ,3,"4.7k","Resistor_SMD:R_0603_1608Metric","~","UNI-ROYAL(Uniroyal Elec)","0603WAF4701T5E",""
SW1 ,1,"A","Button_Switch_SMD:SW_SPST_PTS810","~","C&K","PTS810SJK250SMTRLFS",""
SW2 ,1,"B","Button_Switch_SMD:SW_SPST_PTS810","~","C&K","PTS810SJK250SMTRLFS",""
SW3 ,1,"X","Button_Switch_SMD:SW_SPST_PTS810","~","C&K","PTS810SJK250SMTRLFS",""
SW4 ,1,"Y","Button_Switch_SMD:SW_SPST_PTS810","~","C&K","PTS810SJK250SMTRLFS",""
SW5 ,1,"RESET","Button_Switch_SMD:SW_SPST_PTS810","~","C&K","PTS810SJK250SMTRLFS",""
TP1 ,1,"RX","Connectors:TestPoint_Large","~"
TP10 ,1,"PA28","Connectors:TestPoint_Large","~"
TP11 ,1,"PA27","Connectors:TestPoint_Large","~"
TP12 ,1,"PA6","Connectors:TestPoint_Large","~"
TP13 ,1,"PB23","Connectors:TestPoint_Large","~"
TP14 ,1,"PA7","Connectors:TestPoint_Large","~"
TP15 ,1,"PA0","Connectors:TestPoint_Large","~"
TP16 ,1,"CLK","Connectors:TestPoint_Large","~"
TP17 ,1,"LE","Connectors:TestPoint_Large","~"
TP18 ,1,"BLK","Connectors:TestPoint_Large","~"
TP2 ,1,"TX","Connectors:TestPoint_Large","~"
TP3 ,1,"DAT","Connectors:TestPoint_Large","~"
TP4 ,1,"PB3","Connectors:TestPoint_Large","~"
TP5 ,1,"PA1","Connectors:TestPoint_Large","~"
TP6 ,1,"PB2","Connectors:TestPoint_Large","~"
TP7 ,1,"PA2","Connectors:TestPoint_Large","~"
TP8 ,1,"PA3","Connectors:TestPoint_Large","~"
TP9 ,1,"PB9","Connectors:TestPoint_Large","~"
U1 U2 ,2,"74HC595","Package_SO:TSSOP-16_4.4x5mm_P0.65mm","http://www.ti.com/lit/ds/symlink/sn74hc595.pdf","Nexperia","74HC595PW\,118",""
U3 U4 ,2,"TLC59025","Package_SO:SSOP-24_3.9x8.7mm_P0.635mm","","Texas Instruments","TLC59282DBQR",""
U5 ,1,"GD25Q32C","Package_SO:SOIC-8_5.23x5.23mm_P1.27mm","","GigaDevice Semicon Beijing","GD25Q32CSIGR",""
U6 ,1,"DW01","Package_TO_SOT_SMD:SOT-23-6","","Guangdong Hottech","DW01",""
U7 ,1,"TLV62569DBV","Package_TO_SOT_SMD:SOT-23-5","http://www.ti.com/lit/ds/symlink/tlv62569.pdf","Texas Instruments","TLV62569DBVR",""
U8 ,1,"PM8205A","Package_TO_SOT_SMD:SOT-23-6","","PN SILICON","PM8205A",""
U9 ,1,"HX4054A","Package_TO_SOT_SMD:SOT-23-5","","HX(hengjiaxing)","HX4054A",""
X1 ,1,"#badgelife","badgelife_sao_v169bis:Badgelife-SAOv169-BADGE-2x3",""

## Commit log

2020-09-13 Initial commit
    KiCon 2020 Virtual Badge template
2020-09-21 Added schematic, board and gerbers for my fork
2020-09-24 gregdavill: Initial commit of new badge design
2020-09-24 Tidy up design
2020-09-24 update render
2020-09-24 update readme with new image
2020-09-25 add BOM
2020-10-07 Improve folder structure
2020-10-11 firmware: Add baremetal blinky
2020-10-11 firmware: Add low level SPI code.
2020-10-12 firmware: Add BCM modulation

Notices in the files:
badge.kicad_pcb:
CC-BY-SA
